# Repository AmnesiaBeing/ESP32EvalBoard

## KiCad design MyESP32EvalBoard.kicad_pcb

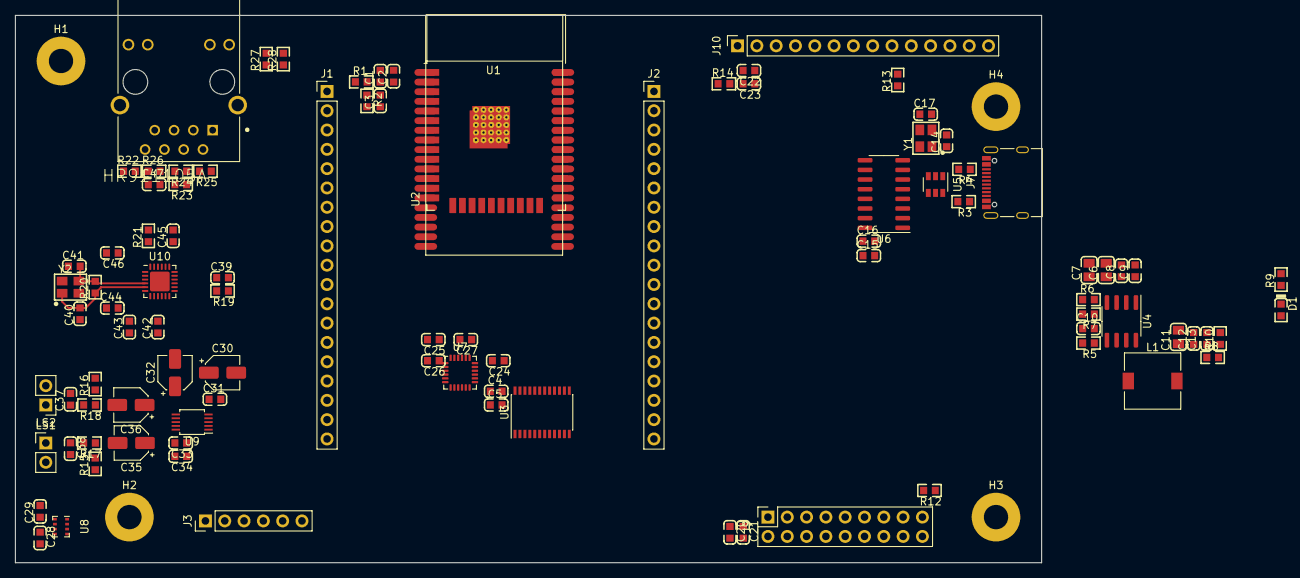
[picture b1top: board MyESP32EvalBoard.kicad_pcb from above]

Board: 4 copper layers, 135.0 x 72.0 mm, 99 parts (0 on the bottom side), 79 nets.

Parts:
C1, C5, C9, C10, C16, C21, C23, C24, C25, C26, C28, C29, C31, C33, C42, C45, C46: 0603_100nF__104_10%_50V; 0603_C
C2, C3, C4, C8, C13, C34, C37, C38, C44: 0603_1uF__105_10%_50V; 0603_C
C6, C7, C11: 0805_22uF__226_20%_25V; 0805_C
C12, C20, C22: 0603_10uF__106_10%_10V; 0603_C
C14, C17: 0603_20pF__200_5%_50V; 0603_C
C15: 0603_22uF__226_20%_6.3V; 0603_C
C27: 0603_2.2nF__222_10%_50V; 0603_C
C30, C35, C36: 3.3uF; CP_Elec_4x5.4
C32: 10uF; CP_Elec_4x5.3
C39: 0603_220nF__224_10%_25V; 0603_C
C40, C41: 0603_18pF__180_5%_50V; 0603_C
C43: 0603_470pF__471_10%_50V; 0603_C
C47: 0603_22nF__223_10%_50V; 0603_C
D1: 0603_绿灯; 0603_LED_S1
H1, H2, H3, H4: MountingHole_Pad; MountingHole_3.2mm_M3_Pad
J1, J2: Conn_01x19_Male; PinHeader_1x19_P2.54mm_Vertical
J3: Conn_01x06_Male; PinHeader_1x06_P2.54mm_Vertical
J7: USB_C_Receptacle_USB2.0; USB_C_Receptacle_Palconn_UTC16-G
J9: Conn_02x09_Odd_Even; PinSocket_2x09_P2.54mm_Vertical
J10: Conn_01x14_Female; PinSocket_1x14_P2.54mm_Vertical
J11: HR911105A; HANRUN_HR911105A
L1: 4.7uH; L_7.3x7.3_H3.5
LS1, LS2: Speaker; PinHeader_1x02_P2.54mm_Vertical
R1, R8, R10, R13, R14: 0603_0Ω__0R0_1%; 0603_R
R2, R7, R12, R15, R16, R19: 0603_10KΩ__1002_1%; 0603_R
R3, R4: 0603_5.1KΩ__5101_1%; 0603_R
R5: 0603_1.5KΩ__1501_1%; 0603_R
R6: 0603_33KΩ__3302_1%; 0603_R
R9, R27, R28: 0603_1KΩ__1001_1%; 0603_R
R17, R18: 0603_470Ω__4700_1%; 0603_R
R20: 0603_1MΩ__1004_1%; 0603_R
R21: 0603_12.1KΩ__1212_1%; 0603_R
R22, R23, R24, R25: 0603_49.9Ω__49R9_1%; 0603_R
R26: 0603_10Ω__10R0_1%; 0603_R
U1: ESP32-WROVER
U2: ESP32-WROOM-32D; ESP32-WROOM-32
U3: PCA9535PW; TSSOP-24_4.4x7.8mm_P0.65mm
U4: AOZ1031; SOIC-8_3.9x4.9mm_P1.27mm
U5: SRV05-4; SOT-23-6
U6: CH340G; SOIC-16_3.9x9.9mm_P1.27mm
U7: MPU-6050; InvenSense_QFN-24_4x4mm_P0.5mm
U8: BMP280; Bosch_LGA-8_2x2.5mm_P0.65mm_ClockwisePinNumbering
U9: CS4344; TSSOP-10_3x3mm_P0.5mm
U10: LAN8720A; QFN-24-1EP_4x4mm_P0.5mm_EP2.6x2.6mm
Y1: SMD-3225_4P__12MHZ_20PF_10PPM; SMD-3225_4P
Y2: SMD-3225_4P__25MHZ_12PF_10PPM; SMD-3225_4P

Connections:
/CAMERA OV2640/OV_PWDN: J9.17, R12.2
/ESP32MCU/ESP32_EN: C3.1, J1.3, R2.2, U1.3, U2.3
/ESP32MCU/ESP32_IO0: J2.14, U1.25, U2.25
/ESP32MCU/ESP32_IO2: J2.15, U1.24, U2.24
/ESP32MCU/ESP32_IO4: J2.13, U1.26, U2.26
/ESP32MCU/ESP32_IO5: J2.10, U1.29, U2.29
/ESP32MCU/ESP32_IO6: J2.19, U1.20, U2.20
/ESP32MCU/ESP32_IO7: J2.18, U1.21, U2.21
/ESP32MCU/ESP32_IO8: J2.17, U1.22, U2.22
/ESP32MCU/ESP32_IO9: J1.17, U1.17, U2.17
/ESP32MCU/ESP32_IO10: J1.18, U1.18, U2.18
/ESP32MCU/ESP32_IO11: J1.19, U1.19, U2.19
/ESP32MCU/ESP32_IO12: J1.14, J3.3, U1.14, U2.14
/ESP32MCU/ESP32_IO13: J1.16, J3.4, U1.16, U2.16
/ESP32MCU/ESP32_IO14: J1.13, J3.2, U1.13, U2.13
/ESP32MCU/ESP32_IO15: J2.16, J3.5, U1.23, U2.23
/ESP32MCU/ESP32_IO16: J2.12, U1.27, U2.27
/ESP32MCU/ESP32_IO17: J2.11, U1.28, U2.28
/ESP32MCU/ESP32_IO18: J2.9, U1.30, U2.30
/ESP32MCU/ESP32_IO19: J2.8, U1.31, U2.31
/ESP32MCU/ESP32_IO21: J2.6, U1.33, U2.33
/ESP32MCU/ESP32_IO22: J2.3, U1.36, U2.36
/ESP32MCU/ESP32_IO23: J2.2, U1.37, U2.37
/ESP32MCU/ESP32_IO25: J1.10, U1.10, U2.10
/ESP32MCU/ESP32_IO26: J1.11, U1.11, U2.11
/ESP32MCU/ESP32_IO27: J1.12, U1.12, U2.12
/ESP32MCU/ESP32_IO32: J1.8, U1.8, U2.8
/ESP32MCU/ESP32_IO33: J1.9, U1.9, U2.9
/ESP32MCU/ESP32_IO34: J1.6, U1.6, U2.6
/ESP32MCU/ESP32_IO35: J1.7, U1.7, U2.7
/ESP32MCU/ESP32_IO36: J1.4, U1.4, U2.4
/ESP32MCU/ESP32_IO39: J1.5, U1.5, U2.5
/ESP32MCU/ESP32_VDD: C1.1, C2.1, R1.2, R2.1, U1.2, U2.2
/Ethernet/ETH_LEDG: R27.1, U10.2
/Ethernet/ETH_LEDY: R28.1, U10.3
/Ethernet/ETH_RX+: J11.3, R23.2, U10.23
/Ethernet/ETH_RX-: J11.6, R22.2, U10.22
/Ethernet/ETH_TX+: J11.1, R25.2, U10.21
/Ethernet/ETH_TX-: J11.2, R24.2, U10.20
/Ethernet/RST: C39.1, R19.2, U10.15
/Power and USB UART/FB: R6.2, R7.1, U4.4
/Power and USB UART/RXD: J2.4, U1.35, U2.35, U6.3
/Power and USB UART/TXD: J2.5, U1.34, U2.34, U6.2
/Power and USB UART/USB+: J7.A6, J7.B6, U5.6, U6.5
/Power and USB UART/USB-: J7.A7, J7.B7, U5.1, U6.6
/SPI LCD and Touch/LCD_BL: J10.9, R13.2
/SPI LCD and Touch/LCD_VCC: C22.2, C23.2, J10.1, R13.1, R14.2
GND: C1.2, C2.2, C3.2, C4.1, C5.1, C6.2, C7.2, C8.2, C9.2, C10.2, C11.2, C12.2, C13.2, C14.2, C15.2, C16.2, C17.2, C20.1, C21.1, C22.1, C23.1, C24.2, C25.2, C26.2, C27.2, C28.2, C29.2, C30.2, C31.2, C32.2, C33.2, C34.2, C37.2, C38.2, C39.2, C40.1, C41.1, C42.1, C43.1, C44.1, C45.2, C46.2, C47.1, H1.1, H2.1, H3.1, H4.1, J1.1, J1.15, J2.1, J2.7, J3.6, J7.A1, J7.A12, J7.B1, J7.B12, J7.S1, J9.1, J10.2, J11.8, J11.10, J11.11, J11.15, J11.16, LS1.2, LS2.2, R3.2, R4.2, R7.2, R9.2, R12.1, R15.1, R16.2, R21.2, U1.1, U1.15, U1.38, U1.39, U2.1, U2.15, U2.38, U3.12, U4.1, U4.3, U5.2, U7.9, U7.18, U8.1, U8.5, U8.7, U9.8, U10.25
I2C_SCL: J9.3, U3.22, U7.23, U8.4
I2C_SDA: J9.5, U3.23, U7.24, U8.3
unnamed: C10.1, R5.2
unnamed: C11.1, C12.1, C13.1, L1.2, R6.1, R8.1
unnamed: C14.1, U6.7, Y1.1
unnamed: C17.1, U6.8, Y1.3
unnamed: C26.1, U7.10
unnamed: C27.1, U7.20
unnamed: C30.1, C31.1, U9.5
unnamed: C32.1, U9.6
unnamed: C35.1, U9.10
unnamed: C35.2, R15.2, R17.1
unnamed: C36.1, U9.7
unnamed: C36.2, R16.1, R18.1
unnamed: C37.1, LS2.1, R18.2
unnamed: C38.1, LS1.1, R17.2
unnamed: C40.2, R20.1, U10.5, Y2.1
unnamed: C41.2, R20.2, U10.4, Y2.3
unnamed: C43.2, C44.2, U10.6
unnamed: C47.2, J11.4, J11.5, R26.2
unnamed: D1.K, R9.1
unnamed: J7.A5, R3.1
unnamed: J7.B5, R4.1
unnamed: J11.9, R27.2
unnamed: J11.12, R28.2
unnamed: L1.1, U4.7, U4.8
unnamed: R5.1, U4.5
unnamed: R21.1, U10.24
VBUS: C6.1, C7.1, C8.1, C9.1, J7.A4, J7.A9, J7.B4, J7.B9, U4.2, U4.6
VDD: C4.2, C5.2, C15.1, C16.1, C20.2, C21.2, C24.1, C28.1, C42.2, D1.A, J1.2, J3.1, J9.2, R1.1, R8.2, R10.1, R14.1, R19.1, U3.24, U5.5, U6.4, U6.16, U7.8, U8.2, U8.6, U10.9
VDDA: C25.1, C29.1, C33.1, C34.1, C45.1, C46.1, R10.2, R22.1, R23.1, R24.1, R25.1, R26.1, U7.13, U8.8, U9.9, U10.1, U10.19

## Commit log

2019-11-12 初次创建仓库
2019-11-12 学习使用git submodule
2019-11-13 20191112未完成的工作
2019-11-13 20191113未完工
2019-11-13 遇到了kicad奇怪的bug，应该修复了？
2019-11-13 20191113
2019-11-14 20191114
